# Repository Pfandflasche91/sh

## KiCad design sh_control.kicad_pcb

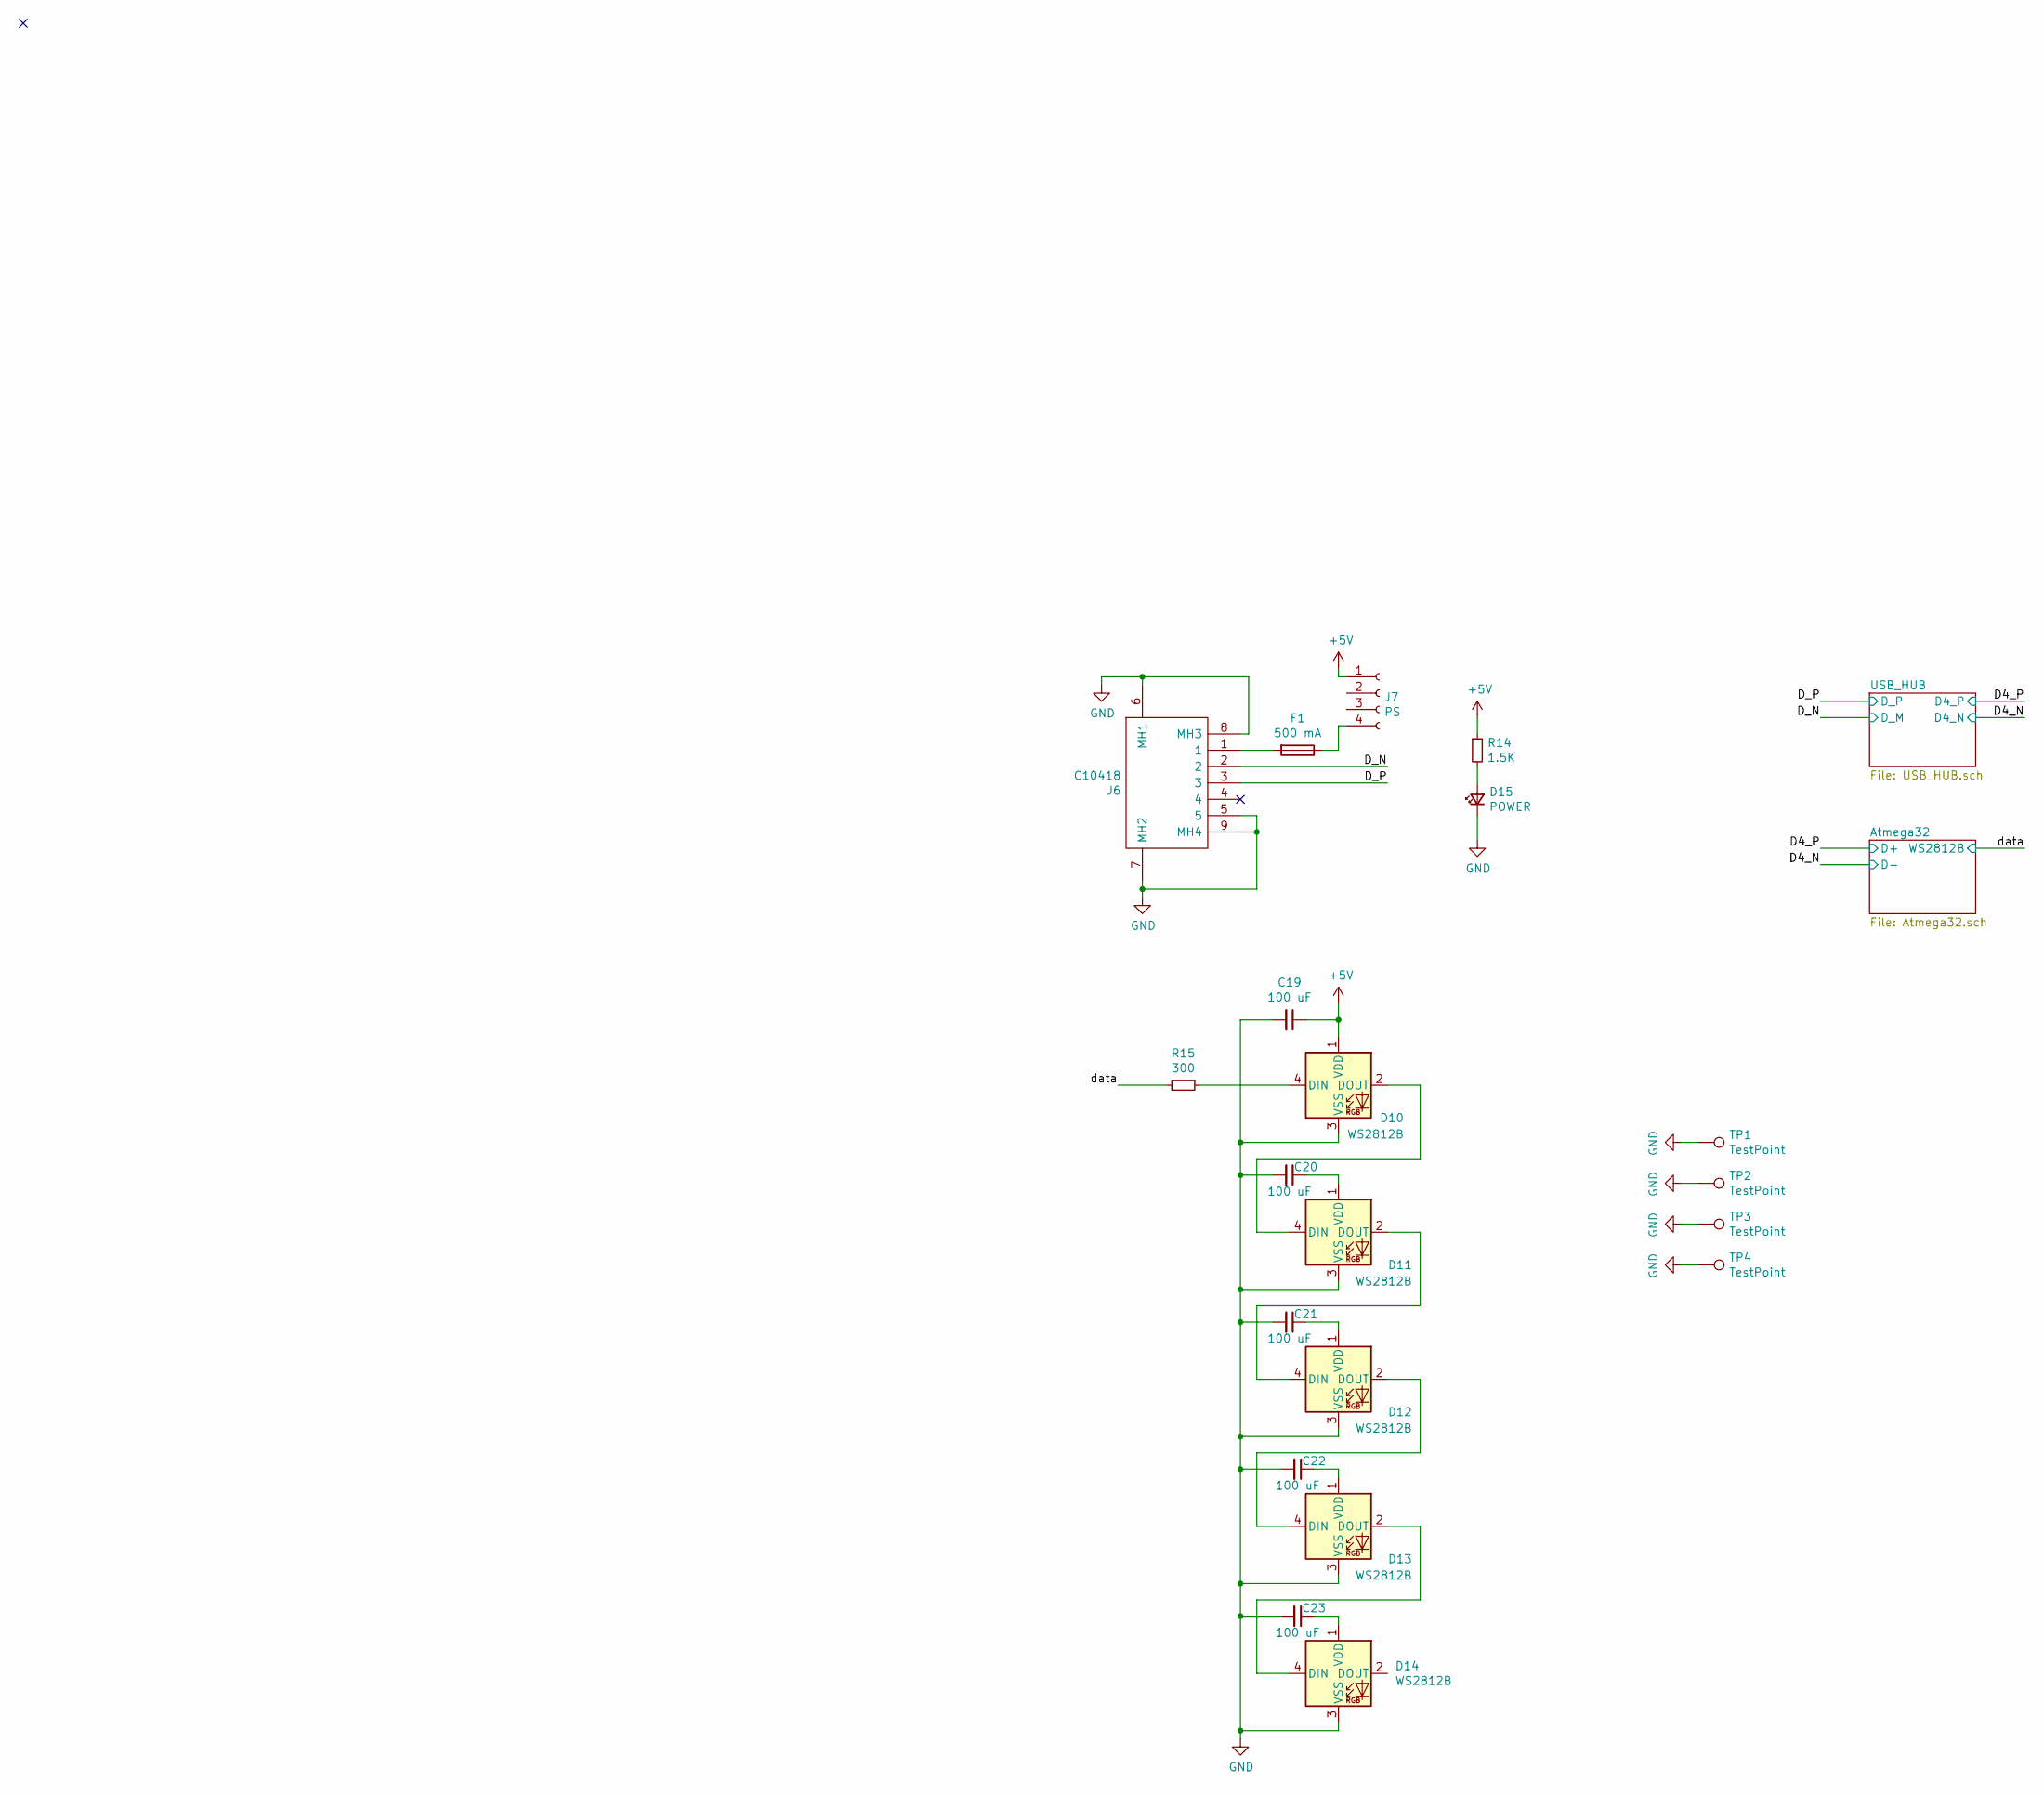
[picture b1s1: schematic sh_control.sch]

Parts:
C19, C20, C21, C22, C23: 100 uF; C_1210_3225Metric; LCSC Part # C90143
D10, D11, D12, D13, D14: WS2812B; LED_WS2812B_PLCC4_5.0x5.0mm_P3.2mm
D15: POWER; LED_0603_1608Metric; LCSC Part # C72043
F1: 500 mA; Fuse_1812_4532Metric; LCSC Part # C117855
J6: C10418; Manufacturer_Part_Number C10418; LCSC Part # C10418
J7: PS; JST_XH_S4B-XH-A-1_1x04_P2.50mm_Horizontal; LCSC Part # C163037
R14: 1.5K; R_0603_1608Metric; LCSC Part # C22843
R15: 300; R_0603_1608Metric; LCSC Part # C23138
TP1, TP2, TP3, TP4: TestPoint; MountingHole_2.2mm_M2_Pad_Via

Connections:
+5V: C19.1, D10.1 (VDD), J7.1, R14.1; also elsewhere on the board
/D_N: J6.2; also elsewhere on the board
/D_P: J6.3; also elsewhere on the board
/data: R15.2; also elsewhere on the board
GND: C19.2, C20.2, C21.2, C22.2, C23.2, D10.3 (VSS), D11.3 (VSS), D12.3 (VSS), D13.3 (VSS), D14.3 (VSS), D15.1 (K), J6.5, J6.6 (MH1), J6.7 (MH2), J6.8 (MH3), J6.9 (MH4), TP1.1, TP2.1, TP3.1, TP4.1; also elsewhere on the board
unnamed: C20.1, D11.1 (VDD)
unnamed: C21.1, D12.1 (VDD)
unnamed: C22.1, D13.1 (VDD)
unnamed: C23.1, D14.1 (VDD)
unnamed: D10.2 (DOUT), D11.4 (DIN)
unnamed: D10.4 (DIN), R15.1
unnamed: D11.2 (DOUT), D12.4 (DIN)
unnamed: D12.2 (DOUT), D13.4 (DIN)
unnamed: D13.2 (DOUT), D14.4 (DIN)
unnamed: D15.2 (A), R14.2
unnamed: F1.1, J7.4
unnamed: F1.2, J6.1

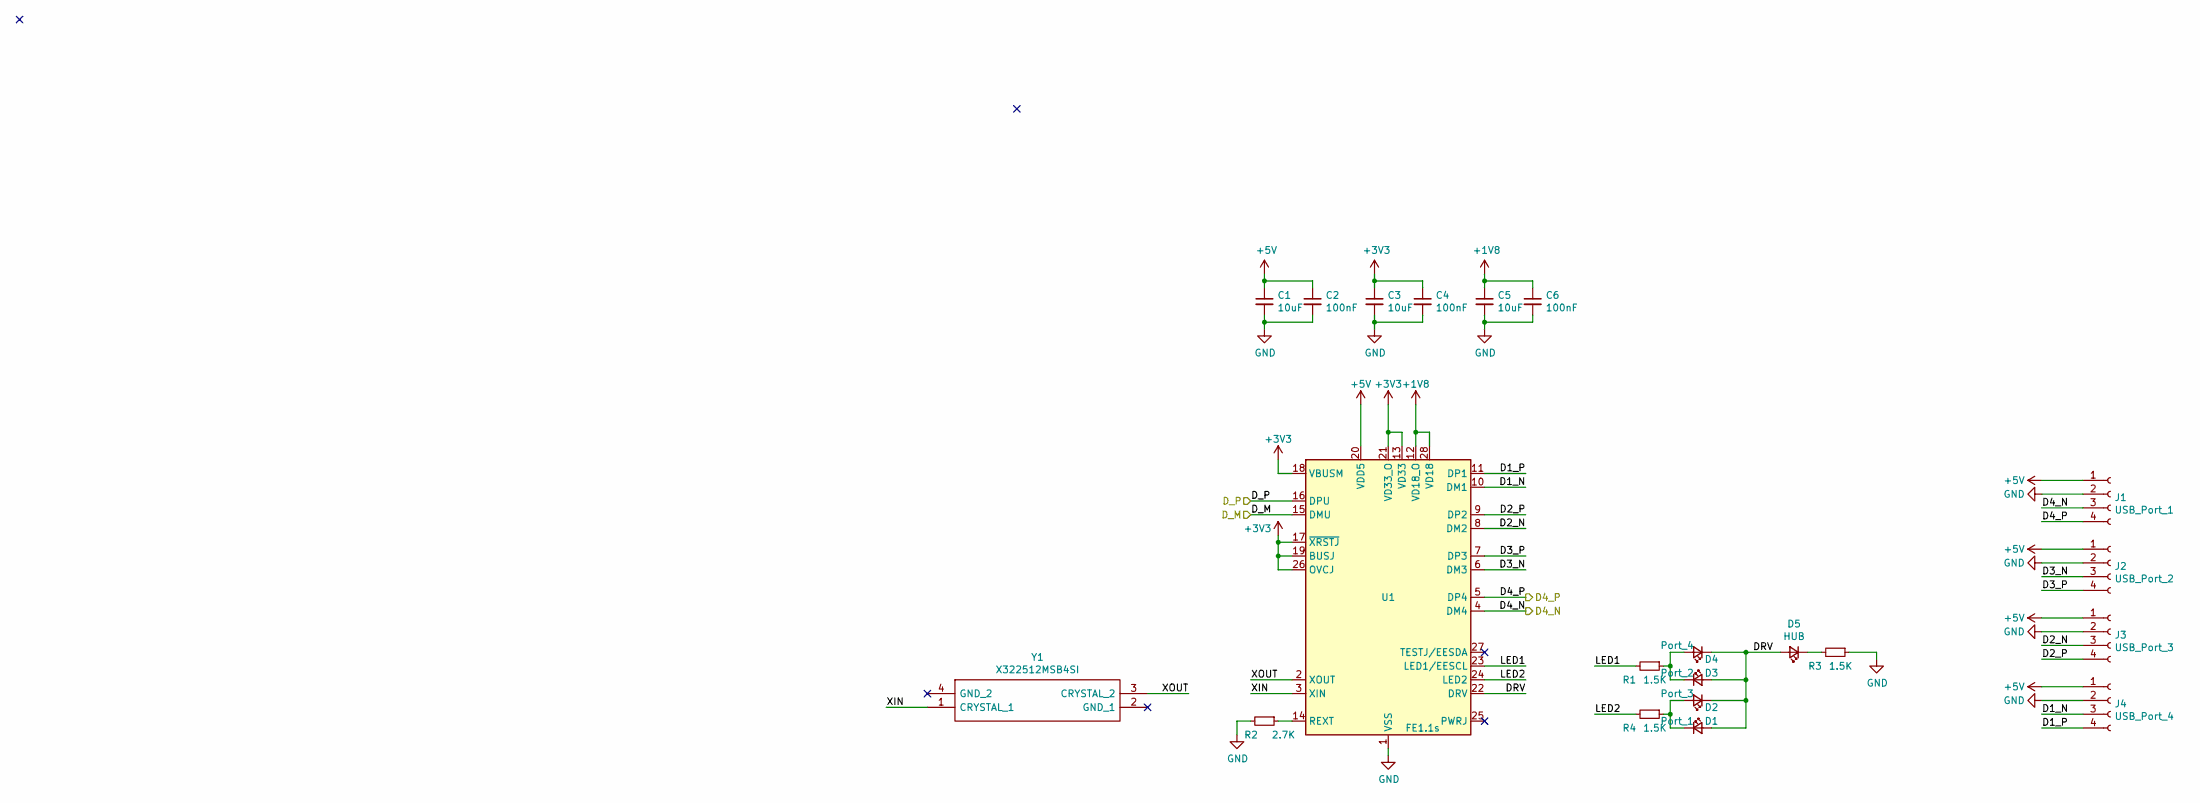
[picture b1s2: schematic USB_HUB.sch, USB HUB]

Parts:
C1, C3, C5: 10uF; C_0805_2012Metric; LCSC Part # C15850
C2, C4, C6: 100nF; C_0603_1608Metric; LCSC Part # C14663
D1: Port_1; LED_0603_1608Metric; LCSC Part # C72041
D2: Port_3; LED_0603_1608Metric; LCSC Part # C72041
D3: Port_2; LED_0603_1608Metric; LCSC Part # C72041
D4: Port_4; LED_0603_1608Metric; LCSC Part # C72041
D5: HUB; LED_0805_2012Metric_Castellated; LCSC Part # C2297
J1: USB_Port_1; JST_XH_S4B-XH-A-1_1x04_P2.50mm_Horizontal; LCSC Part # C163037
J2: USB_Port_2; JST_XH_S4B-XH-A-1_1x04_P2.50mm_Horizontal; LCSC Part # C163037
J3: USB_Port_3; JST_XH_S4B-XH-A-1_1x04_P2.50mm_Horizontal; LCSC Part # C163037
J4: USB_Port_4; JST_XH_S4B-XH-A-1_1x04_P2.50mm_Horizontal; LCSC Part # C163037
R1, R3, R4: 1.5K; R_0603_1608Metric; LCSC Part # C22843
R2: 2.7K; R_0603_1608Metric; LCSC Part # C13167
U1: FE1.1s; SSOP-28_3.9x9.9mm_P0.635mm
Y1: X322512MSB4SI; Manufacturer_Part_Number X322512MSB4SI; LCSC Part # C9002

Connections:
+1V8: C5.1, C6.1, U1.12 (VD18_O), U1.28 (VD18)
+3V3: C3.1, C4.1, U1.13 (VD33), U1.17 (~XRSTJ), U1.18 (VBUSM), U1.19 (BUSJ), U1.21 (VD33_O), U1.26 (OVCJ)
+5V: C1.1, C2.1, J1.1, J2.1, J3.1, J4.1, U1.20 (VDD5); also elsewhere on the board
/D4_N: J1.3, U1.4 (DM4); also elsewhere on the board
/D4_P: J1.4, U1.5 (DP4); also elsewhere on the board
/D_N: U1.15 (DMU); also elsewhere on the board
/D_P: U1.16 (DPU); also elsewhere on the board
/USB_HUB/D1_N: J4.3, U1.10 (DM1)
/USB_HUB/D1_P: J4.4, U1.11 (DP1)
/USB_HUB/D2_N: J3.3, U1.8 (DM2)
/USB_HUB/D2_P: J3.4, U1.9 (DP2)
/USB_HUB/D3_N: J2.3, U1.6 (DM3)
/USB_HUB/D3_P: J2.4, U1.7 (DP3)
/USB_HUB/DRV: D1.2 (A), D2.1 (K), D3.2 (A), D4.1 (K), D5.2 (A), U1.22 (DRV)
/USB_HUB/LED1: R1.2, U1.23 (LED1/EESCL)
/USB_HUB/LED2: R4.2, U1.24 (LED2)
/USB_HUB/XIN: U1.3 (XIN), Y1.1 (CRYSTAL_1)
/USB_HUB/XOUT: U1.2 (XOUT), Y1.3 (CRYSTAL_2)
GND: C1.2, C2.2, C3.2, C4.2, C5.2, C6.2, J1.2, J2.2, J3.2, J4.2, R2.2, R3.1, U1.1 (VSS); also elsewhere on the board
unnamed: D1.1 (K), D2.2 (A), R4.1
unnamed: D3.1 (K), D4.2 (A), R1.1
unnamed: D5.1 (K), R3.2
unnamed: R2.1, U1.14 (REXT)

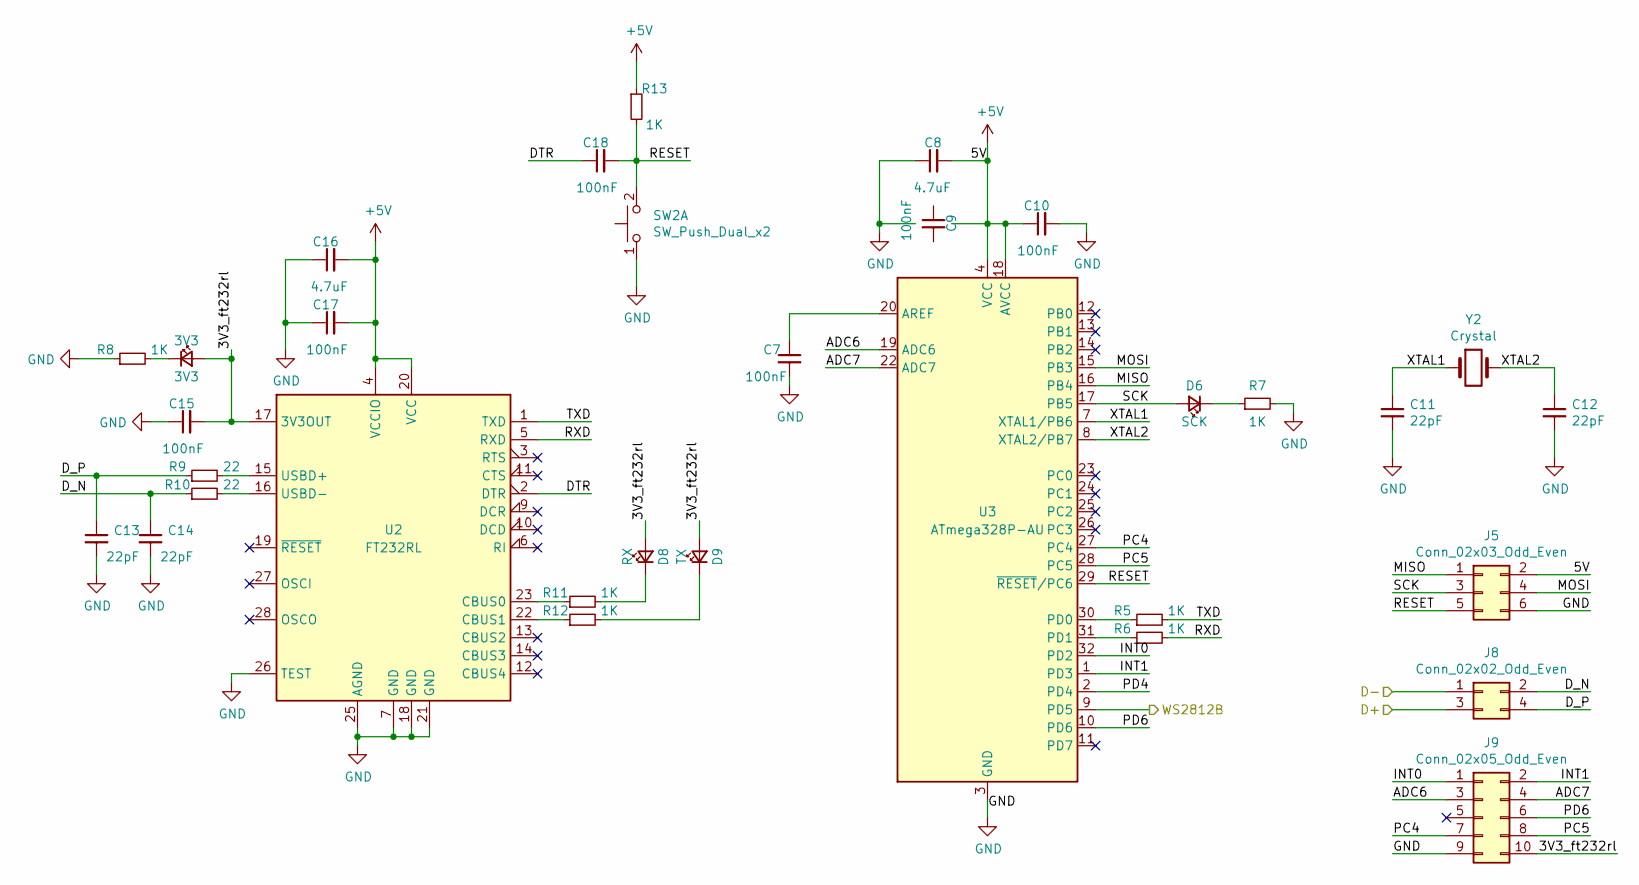
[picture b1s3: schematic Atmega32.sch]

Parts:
3V3: 3V3; LED_0603_1608Metric; LCSC Part # C72043
C7, C9, C10, C15, C17, C18: 100nF; C_0603_1608Metric; LCSC Part # C14663
C8, C16: 4.7uF; C_1206_3216Metric; LCSC Part # C29823
C11, C12, C13, C14: 22pF; C_0603_1608Metric; LCSC Part # C1603
D6: SCK; LED_0603_1608Metric; LCSC Part # C2286
D8: RX; LED_0603_1608Metric; LCSC Part # C2286
D9: TX; LED_0603_1608Metric; LCSC Part # C2286
J5: Conn_02x03_Odd_Even; PinHeader_2x03_P2.00mm_Vertical; LCSC Part # C225288
J8: Conn_02x02_Odd_Even; PinHeader_2x02_P2.00mm_Vertical; LCSC Part # C225287
J9: Conn_02x05_Odd_Even; PinHeader_2x05_P2.00mm_Vertical; LCSC Part # C225290
R5, R6, R7, R8, R11, R12, R13: 1K; R_0603_1608Metric; LCSC Part # C21190
R9, R10: 22; R_0603_1608Metric; LCSC Part # C23345
SW2: SW_Push_Dual_x2; SW_PUSH_6mm_H4.3mm
U2: FT232RL; SSOP-28_5.3x10.2mm_P0.65mm
U3: ATmega328P-AU; TQFP-32_7x7mm_P0.8mm; LCSC Part # C14877
Y2: Crystal; Crystal_SMD_HC49-SD

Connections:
+5V: C8.2, C10.1, C16.2, C17.2, J5.2, R13.1, U2.4 (VCCIO), U2.20 (VCC), U3.4 (VCC), U3.6 (VCC), U3.18 (AVCC); also elsewhere on the board
/Atmega32/3V3_ft232rl: 3V3.2 (A), C15.2, D8.2 (A), D9.2 (A), J9.10, U2.17 (3V3OUT)
/Atmega32/ADC6: J9.3, U3.19 (ADC6)
/Atmega32/ADC7: J9.4, U3.22 (ADC7)
/Atmega32/DTR: C18.1, U2.2 (DTR)
/Atmega32/D_N: C14.1, J8.2, R10.1
/Atmega32/D_P: C13.1, J8.4, R9.1
/Atmega32/INT0: J9.1, U3.32 (PD2)
/Atmega32/INT1: J9.2, U3.1 (PD3)
/Atmega32/MISO: J5.1, U3.16 (PB4)
/Atmega32/MOSI: J5.4, U3.15 (PB3)
/Atmega32/PC4: J9.7, U3.27 (PC4)
/Atmega32/PC5: J9.8, U3.28 (PC5)
/Atmega32/PD4: U3.2 (PD4)
/Atmega32/PD6: J9.6, U3.10 (PD6)
/Atmega32/RESET: C18.2, J5.5, R13.2, SW2.2 (D), U3.29 (~RESET~/PC6)
/Atmega32/RXD: R6.2, U2.5 (RXD)
/Atmega32/SCK: D6.2 (A), J5.3, U3.17 (PB5)
/Atmega32/TXD: R5.2, U2.1 (TXD)
/Atmega32/XTAL1: C11.1, U3.7 (XTAL1/PB6), Y2.1
/Atmega32/XTAL2: C12.1, U3.8 (XTAL2/PB7), Y2.2
/D4_N: J8.1; also elsewhere on the board
/D4_P: J8.3; also elsewhere on the board
/data: U3.9 (PD5); also elsewhere on the board
GND: C7.2, C8.1, C10.2, C11.2, C12.2, C13.2, C14.2, C15.1, C16.1, C17.1, J5.6, J9.9, R7.2, R8.1, SW2.1 (C), U2.7 (GND), U2.18 (GND), U2.21 (GND), U2.25 (AGND), U2.26 (TEST), U3.3 (GND), U3.5 (GND), U3.21 (GND); also elsewhere on the board
unnamed: 3V3.1 (K), R8.2
unnamed: C7.1, U3.20 (AREF)
unnamed: D6.1 (K), R7.1
unnamed: D8.1 (K), R11.2
unnamed: D9.1 (K), R12.2
unnamed: R5.1, U3.30 (PD0)
unnamed: R6.1, U3.31 (PD1)
unnamed: R9.2, U2.15 (USBD+)
unnamed: R10.2, U2.16 (USBD-)
unnamed: R11.1, U2.23 (CBUS0)
unnamed: R12.1, U2.22 (CBUS1)

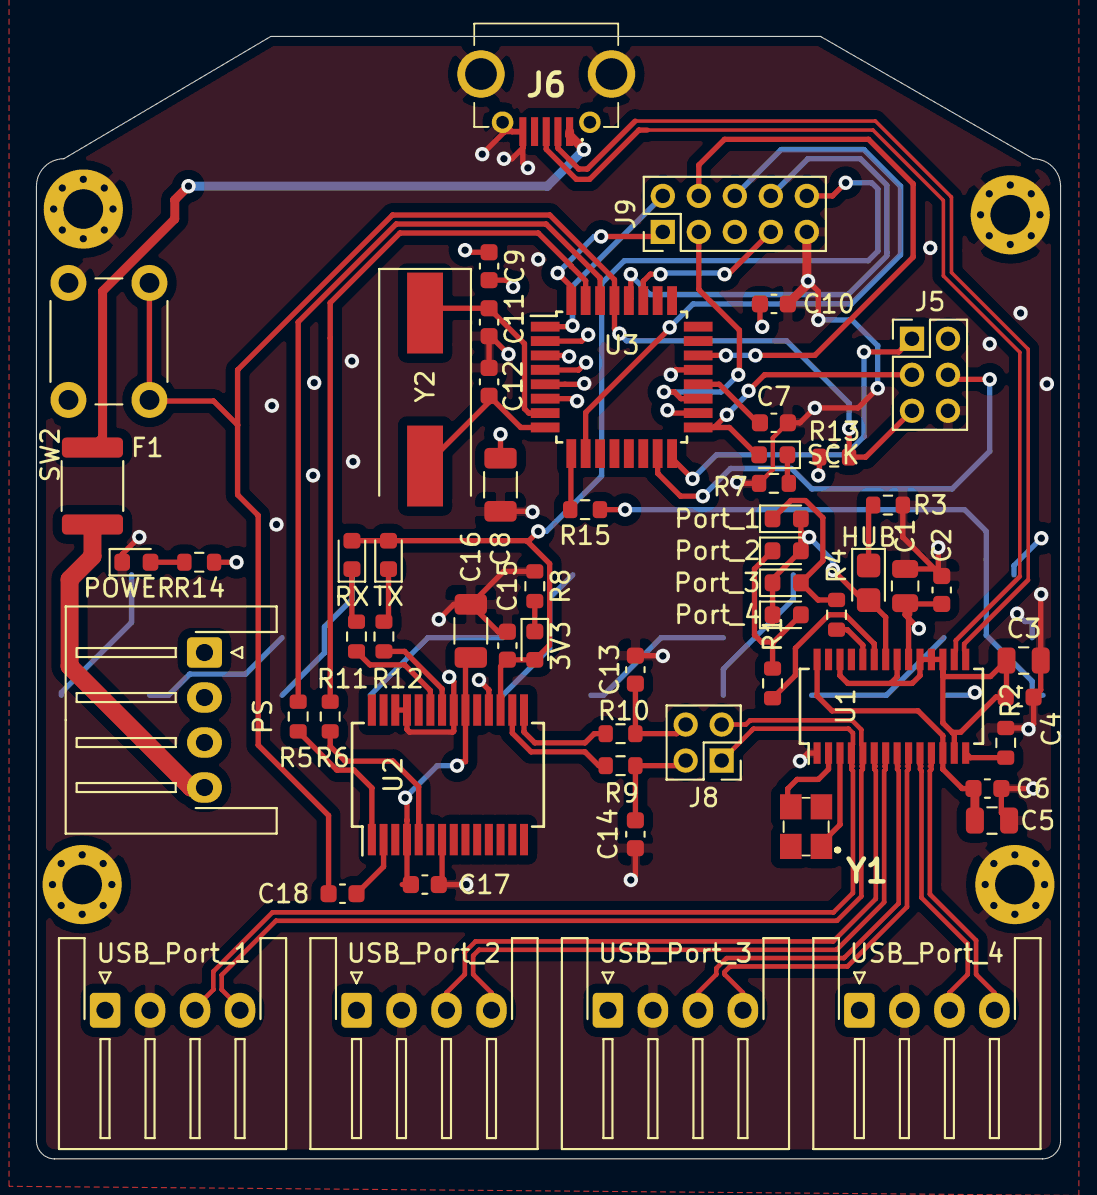
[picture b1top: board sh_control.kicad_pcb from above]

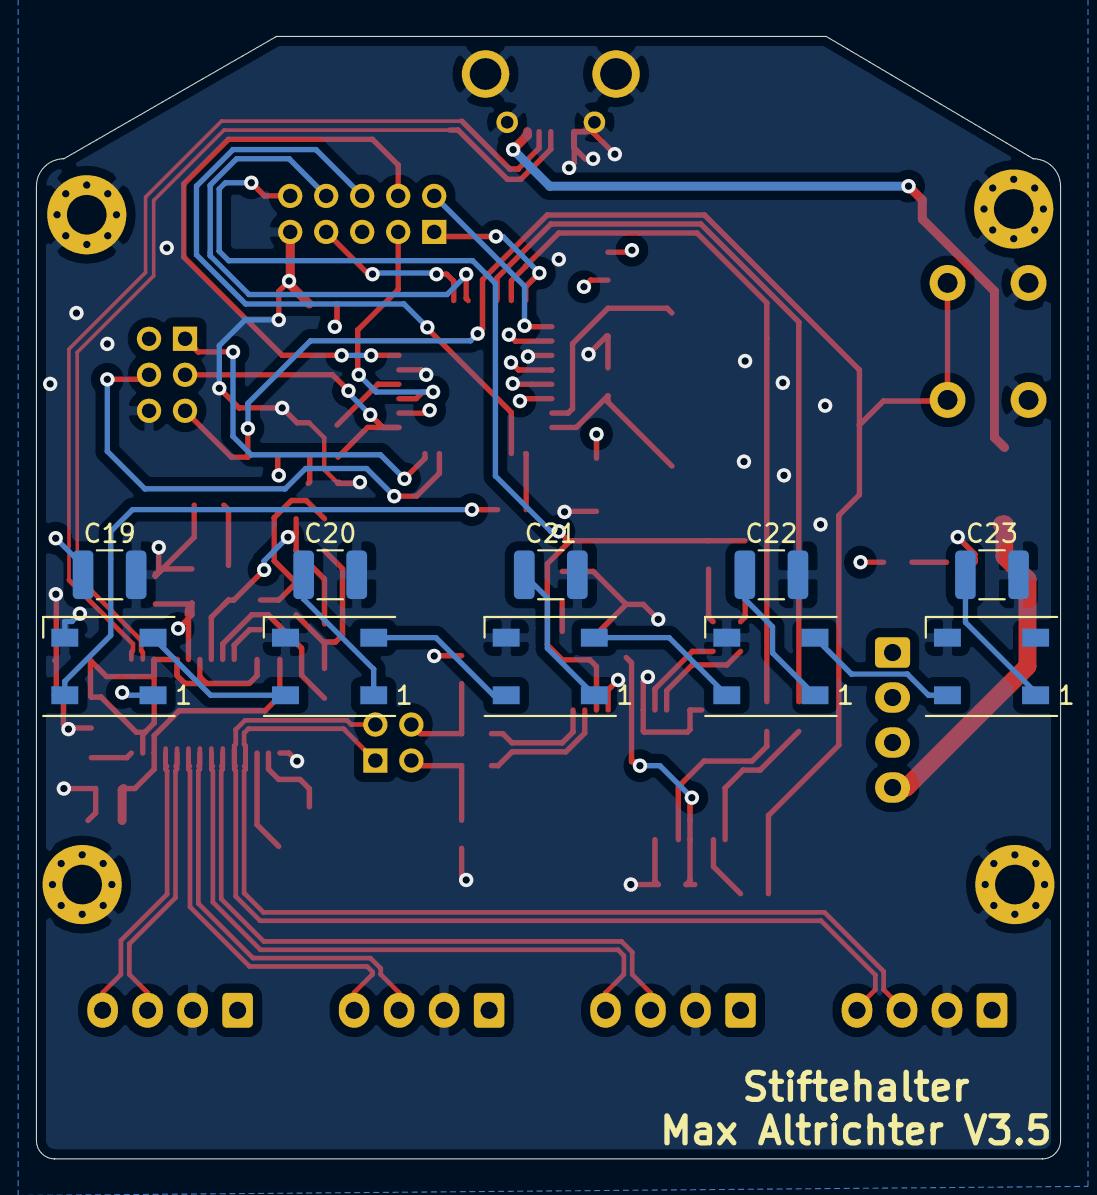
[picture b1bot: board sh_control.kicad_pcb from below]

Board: 4 copper layers, 56.9 x 62.4 mm, 73 parts (10 on the bottom side), 66 nets.

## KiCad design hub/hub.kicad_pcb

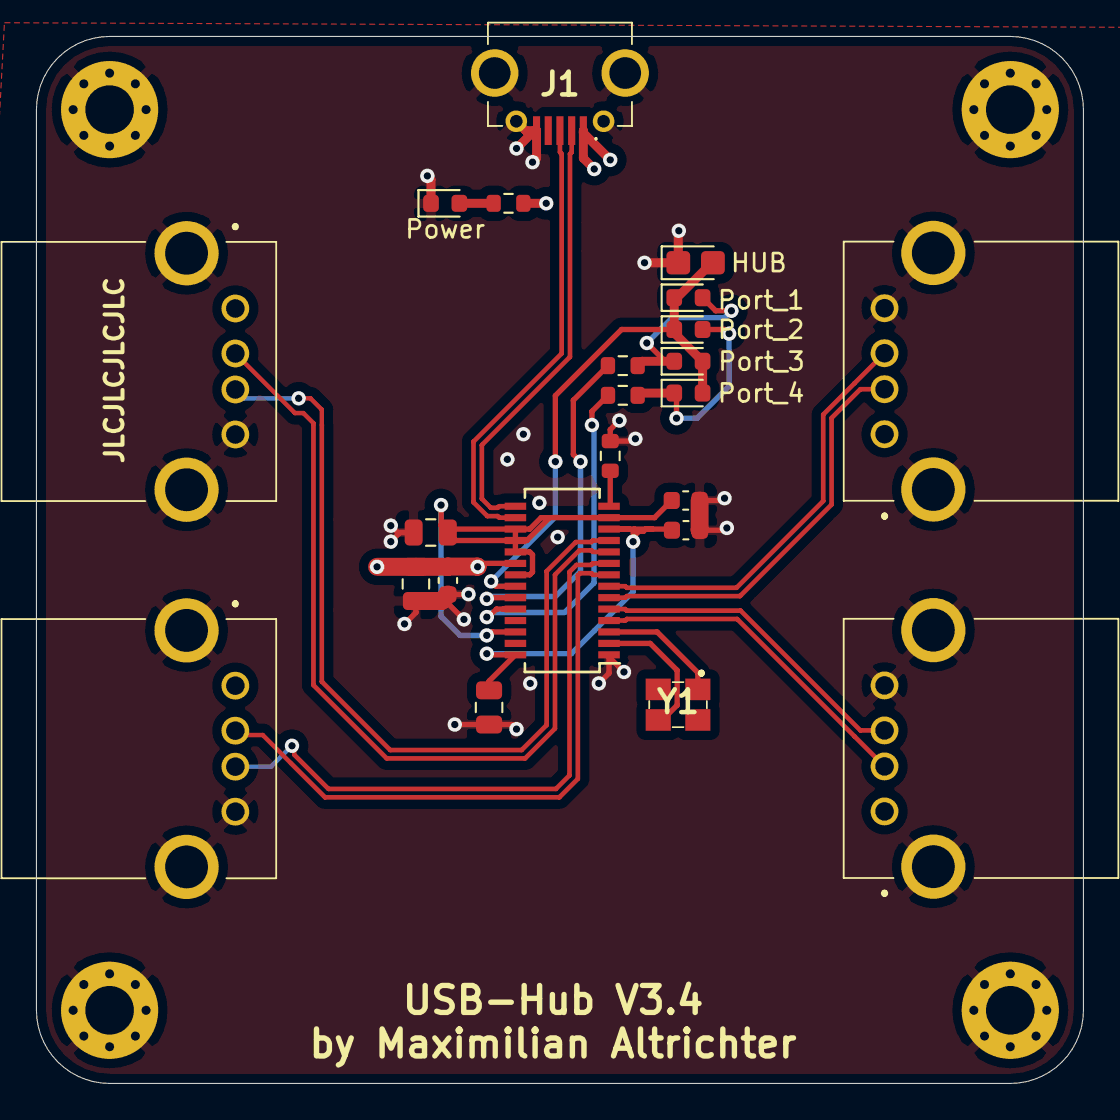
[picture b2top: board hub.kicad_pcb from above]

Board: 4 copper layers, 58.2 x 58.2 mm, 27 parts (0 on the bottom side), 23 nets.

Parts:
C1, C3, C5: 100nF; C_0603_1608Metric
C2, C4, C6: 10uF; C_0805_2012Metric
D1: Power; LED_0603_1608Metric
D2: Port_1; LED_0603_1608Metric
D3: Port_3; LED_0603_1608Metric
D4: Port_2; LED_0603_1608Metric
D5: Port_4; LED_0603_1608Metric
D6: HUB; LED_0805_2012Metric_Castellated
H1, H2, H3, H4: MountingHole_Pad; MountingHole_2.7mm_M2.5_Pad_Via
J1: C10418
J2, J3, J4, J5: USB_A; 676430910
R1, R3, R4: 1.5K; R_0603_1608Metric
R2: 2.7K; R_0603_1608Metric
U1: FE1.1s; SSOP-28_3.9x9.9mm_P0.635mm
Y1: 12 MHZ; X322512MSB4SI

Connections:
+1V8: C5.1, C6.1, U1.12, U1.28
+3V3: C3.1, C4.1, U1.13, U1.17, U1.18, U1.19, U1.21, U1.26
+5V: C1.1, C2.1, J1.1, J2.1, J3.1, J4.1, J5.1, R1.1, U1.20
/D1_N: J2.2, U1.10
/D1_P: J2.3, U1.11
/D2_N: J3.2, U1.8
/D2_P: J3.3, U1.9
/D3_N: J5.2, U1.6
/D3_P: J5.3, U1.7
/D4_N: J4.2, U1.4
/D4_P: J4.3, U1.5
/DRV: D2.1, D3.2, D4.1, D5.2, D6.2, U1.22
/D_N: J1.2, U1.15
/D_P: J1.3, U1.16
/LED_1: R3.1, U1.23
/LED_2: R4.1, U1.24
/XIN: U1.3, Y1.1
/XOUT: U1.2, Y1.3
GND: C1.2, C2.2, C3.2, C4.2, C5.2, C6.2, D1.1, D6.1, H1.1, H2.1, H3.1, H4.1, J1.5, J1.6, J1.7, J1.8, J1.9, J2.4, J2.5, J3.4, J3.5, J4.4, J4.5, J5.4, J5.5, R2.1, U1.1
unnamed: D1.2, R1.2
unnamed: D2.2, D3.1, R3.2
unnamed: D4.2, D5.1, R4.2
unnamed: R2.2, U1.14

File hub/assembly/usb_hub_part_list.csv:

Comment,Designator,Footprint,LCSC
"100nF","C1,C3,C5","Capacitor_SMD:C_0603_1608Metric","C14663"
"10uF","C2,C4,C6","Capacitor_SMD:C_0805_2012Metric","C15850"
"Power","D1","LED_SMD:LED_0603_1608Metric","C72043"
"Port_1","D2","LED_SMD:LED_0603_1608Metric","C72041"
"Port_3","D3","LED_SMD:LED_0603_1608Metric","C72041"
"Port_2","D4","LED_SMD:LED_0603_1608Metric","C72041"
"Port_4","D5","LED_SMD:LED_0603_1608Metric","C72041"
"HUB","D6","LED_SMD:LED_0805_2012Metric_Castellated","C84256"
"1.5K","R1,R3,R4","Resistor_SMD:R_0603_1608Metric","C22843"
"2.7K","R2","Resistor_SMD:R_0603_1608Metric","C13167"
"12 MHZ","Y1","crystal_12MHz:X322512MSB4SI","C9002"
"C10418","J1","usb_b_micro:C10418","C10418"
"USB_A","J2","SamacSys_Parts:676430910","C42664"
"USB_A","J3","SamacSys_Parts:676430910","C42664"
"USB_A","J4","SamacSys_Parts:676430910","C42664"
"USB_A","J5","SamacSys_Parts:676430910","C42664"

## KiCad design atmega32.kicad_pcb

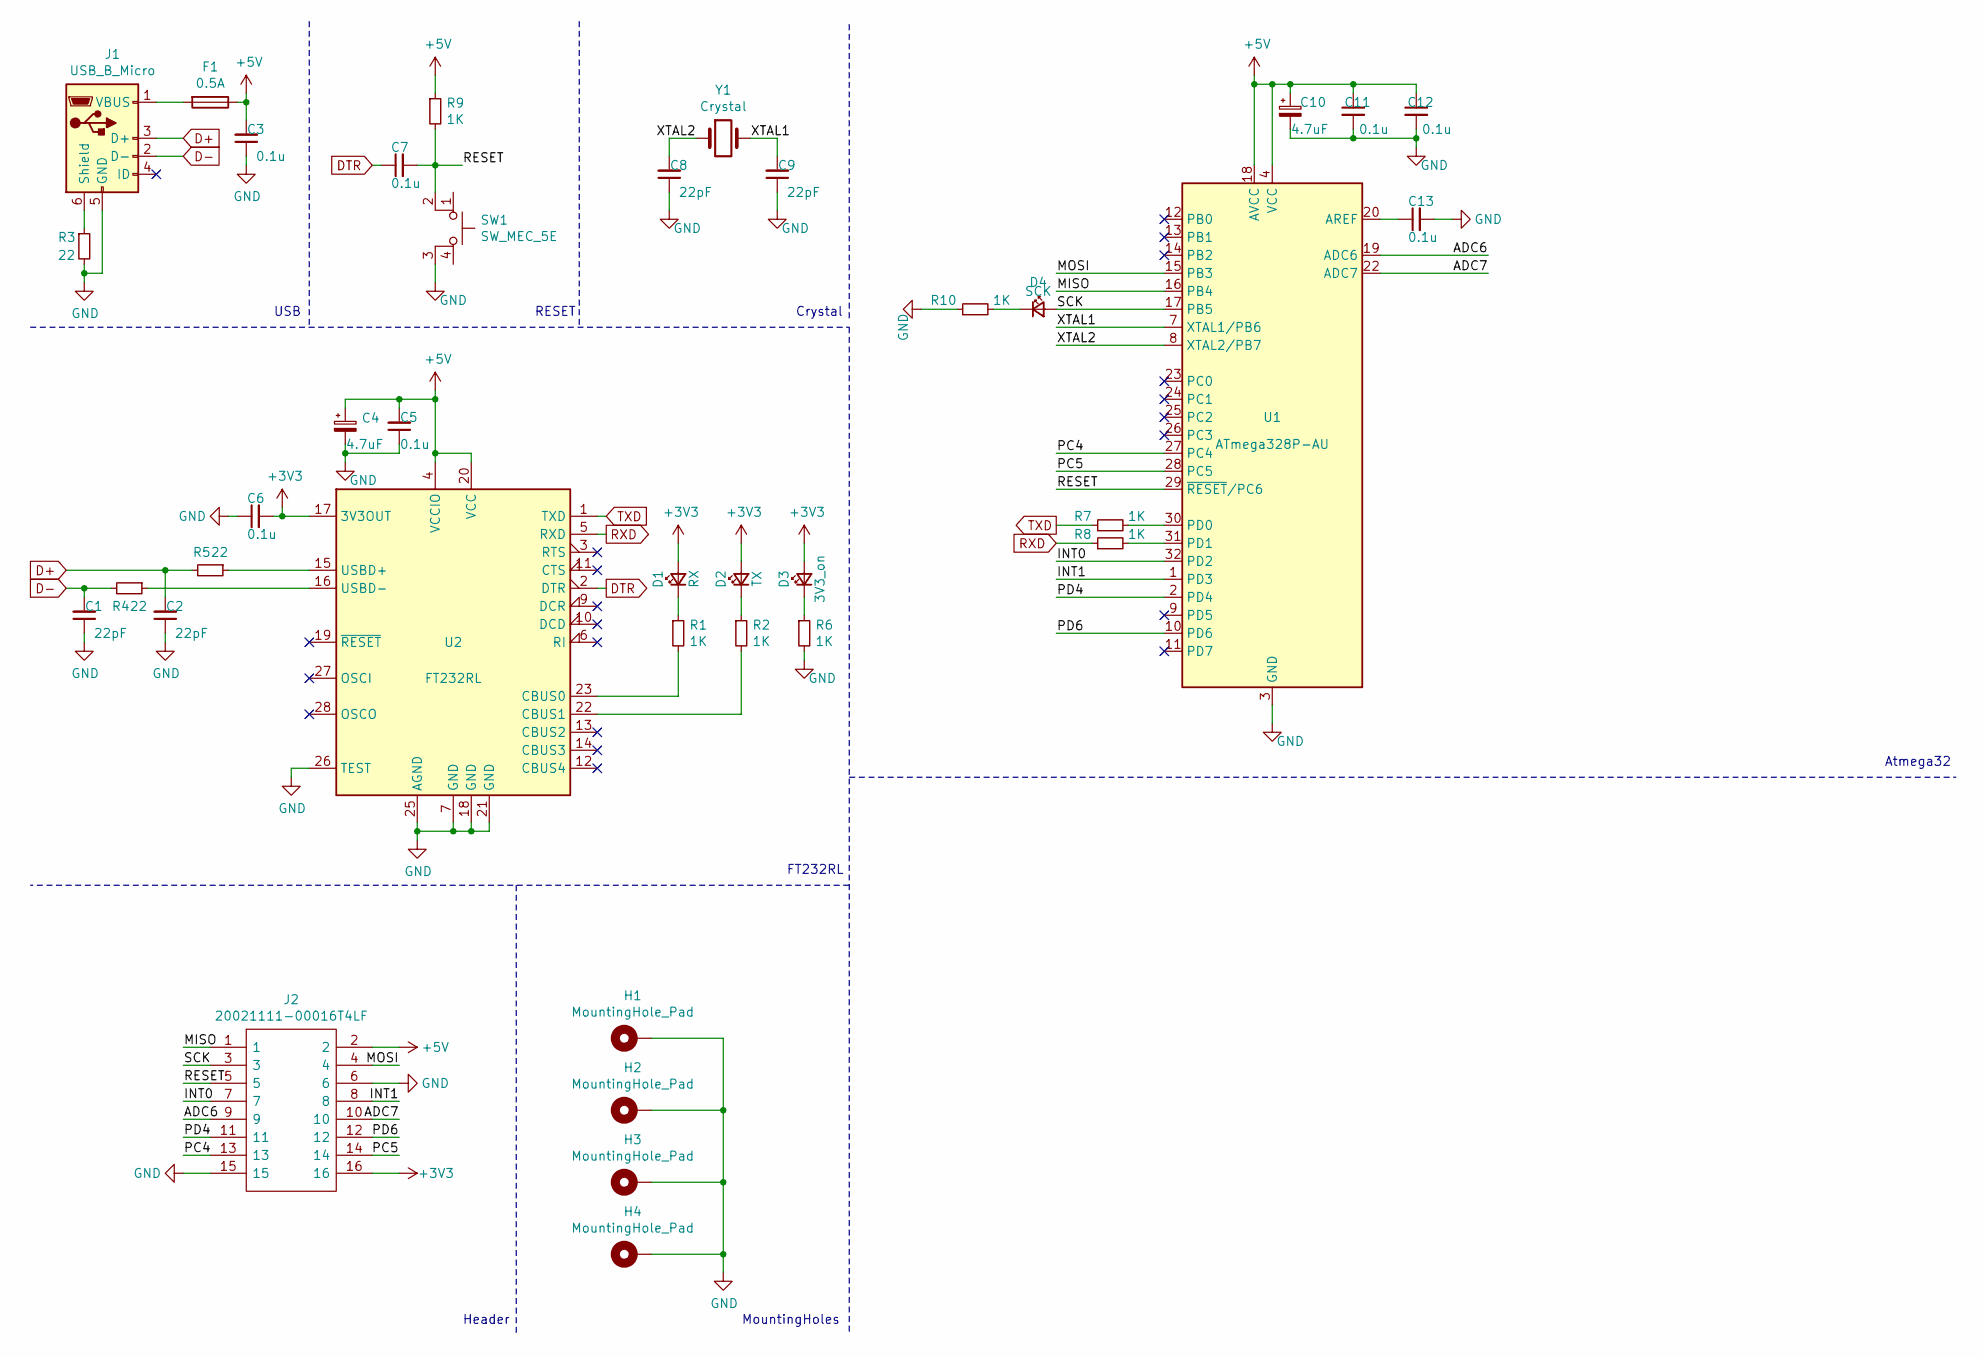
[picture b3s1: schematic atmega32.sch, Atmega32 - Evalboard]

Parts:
C1, C2: 22pF; C_22pF
C3, C5, C6, C7, C11, C12, C13: 0.1u; C_0.1uF
C4, C10: 4.7uF; C_4.7uF
C8, C9: 22pF; C_0.1uF
D1: RX; LED_WL-SMCW
D2: TX; LED_WL-SMCW
D3: 3V3_on; LED_WL-SMCW
D4: SCK; LED_WL-SMCW
F1: 0.5A; F_0.5A
H1, H2, H3, H4: MountingHole_Pad; MountingHole_3.2mm_M3_Pad_Via
J1: USB_B_Micro; USB_Micro-B_Molex-105017-0001
J2: 20021111-00016T4LF; 2002111100016T4LF; Mouser Part Number 649-221111-00016T4LF
R1, R2, R6, R7, R8, R9, R10: 1K; R_1K
R3, R4, R5: 22; R_22
SW1: SW_MEC_5E; Button
U1: ATmega328P-AU; TQFP-32_7x7mm_P0.8mm
U2: FT232RL; SSOP-28_5.3x10.2mm_P0.65mm
Y1: Crystal; ECS49205PXTR

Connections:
+3V3: C6.2, D1.2 (A), D2.2 (A), D3.2 (A), J2.16, U2.17 (3V3OUT)
+5V: C3.2, C4.1, C5.2, C10.1, C11.1, C12.1, F1.1, J2.2, R9.1, U1.4 (VCC), U1.6 (VCC), U1.18 (AVCC), U2.4 (VCCIO), U2.20 (VCC)
/ADC6: J2.9, U1.19 (ADC6)
/ADC7: J2.10, U1.22 (ADC7)
/INT0: J2.7, U1.32 (PD2)
/INT1: J2.8, U1.1 (PD3)
/MISO: J2.1, U1.16 (PB4)
/MOSI: J2.4, U1.15 (PB3)
/PC4: J2.13, U1.27 (PC4)
/PC5: J2.14, U1.28 (PC5)
/PD4: J2.11, U1.2 (PD4)
/PD6: J2.12, U1.10 (PD6)
/RESET: C7.2, J2.5, R9.2, SW1.2, U1.29 (~RESET~/PC6)
/SCK: D4.2 (A), J2.3, U1.17 (PB5)
/XTAL1: C9.2, U1.7 (XTAL1/PB6), Y1.2
/XTAL2: C8.2, U1.8 (XTAL2/PB7), Y1.1
D+: C2.2, J1.3 (D+), R5.2
D-: C1.2, J1.2 (D-), R4.2
DTR: C7.1, U2.2 (DTR)
GND: C1.1, C2.1, C3.1, C4.2, C5.1, C6.1, C8.1, C9.1, C10.2, C11.2, C12.2, C13.2, H1.1, H2.1, H3.1, H4.1, J1.5 (GND), J2.6, J2.15, R3.2, R6.2, R10.1, SW1.3 (K), U1.3 (GND), U1.5 (GND), U1.21 (GND), U2.7 (GND), U2.18 (GND), U2.21 (GND), U2.25 (AGND), U2.26 (TEST)
unnamed: C13.1, U1.20 (AREF)
unnamed: D1.1 (K), R1.1
unnamed: D2.1 (K), R2.1
unnamed: D3.1 (K), R6.1
unnamed: D4.1 (K), R10.2
unnamed: F1.2, J1.1 (VBUS)
unnamed: J1.6 (Shield), R3.1
unnamed: R1.2, U2.23 (CBUS0)
unnamed: R2.2, U2.22 (CBUS1)
unnamed: R4.1, U2.16 (USBD-)
unnamed: R5.1, U2.15 (USBD+)
unnamed: R7.2, U1.30 (PD0)
unnamed: R8.2, U1.31 (PD1)
RXD: R8.1, U2.5 (RXD)
TXD: R7.1, U2.1 (TXD)

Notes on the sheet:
USB
FT232RL
Header
MountingHoles
RESET
Crystal
Atmega32

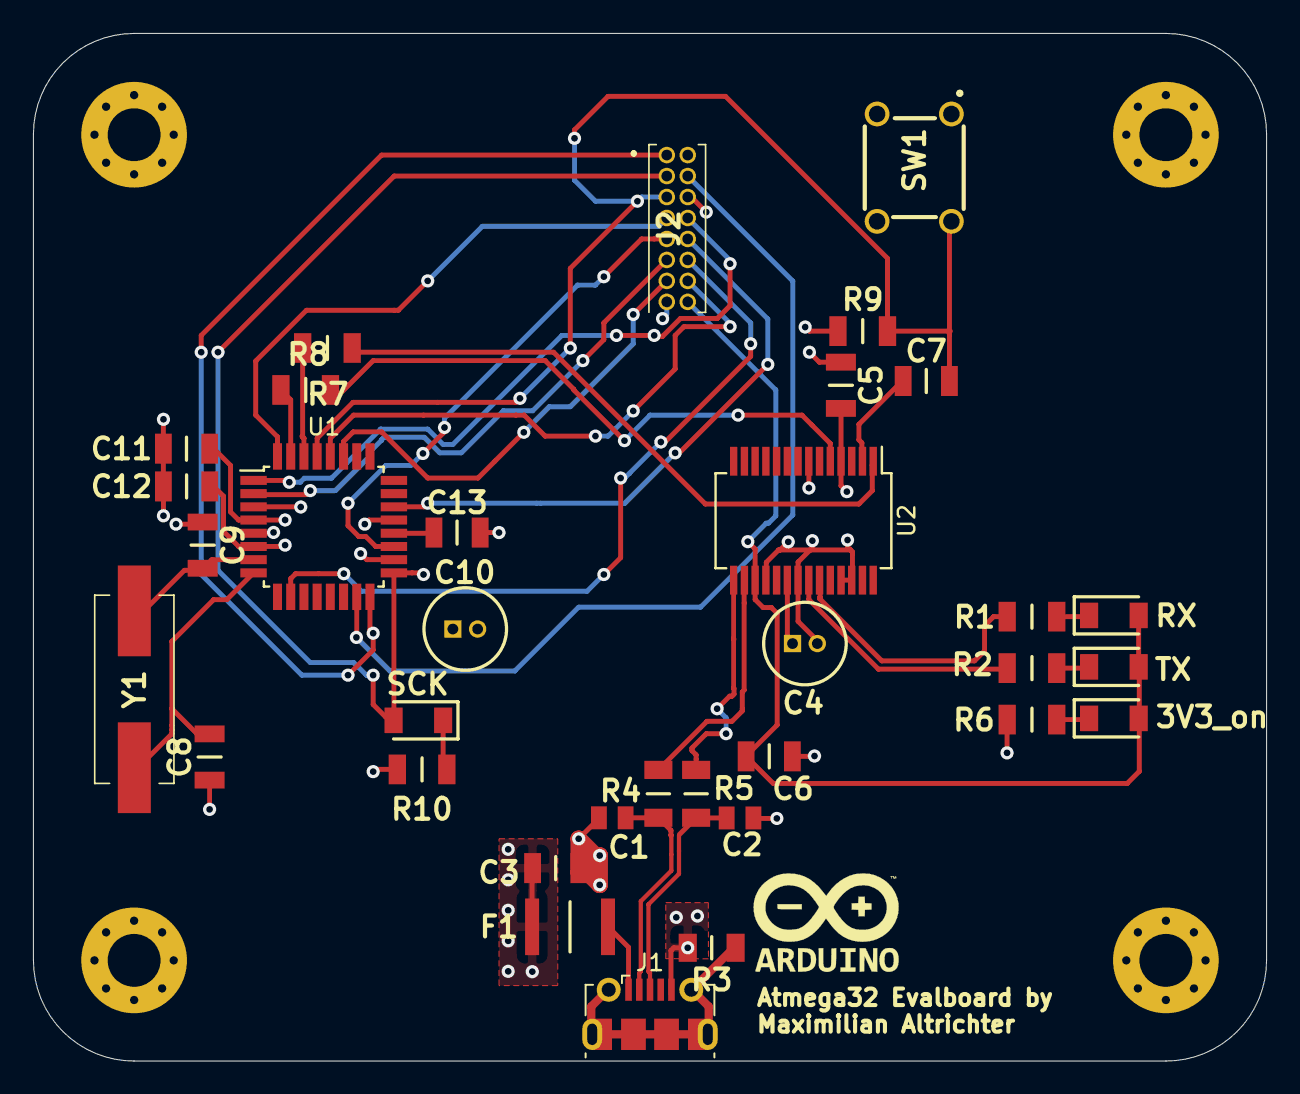
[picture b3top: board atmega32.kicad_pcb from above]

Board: 4 copper layers, 74.7 x 62.2 mm, 38 parts (0 on the bottom side), 35 nets.

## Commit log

2021-04-16 Added KiCAD files
2021-04-28 first assembly, didnt work so well
2021-04-28 deleted all, beginning of eval board
2021-04-28 hub schematic finished
2021-04-29 split in two boards from now on
2021-04-29 new branch, only for usb hub
2021-04-29 finished schematic, placing parts and so on
2021-04-30 finished hub, added reste button
2021-05-01 review passed, bom created
2021-05-01 evalboard for atmeag32
2021-05-01 gerber created -> Finished!!
2021-05-01 new project for atmgea evalboard
2021-05-01 finished eval board
2021-05-02 orderd
2021-05-13 added BOM
2021-05-13 final assembly, WORKING!!!!
2021-05-13 added stepfile
2021-05-24 start V3.3
2021-06-24 changed
2021-08-08 V3.4
2021-08-09 got all parts except usb a
2021-08-09 V3.4 finished and ordered
2021-08-09 V3.4 edit
2021-08-26 sh_control 2.0
    deleted old files and created new project
2021-08-26 USB HUB schematic ready
    added the schematic of the USB HUB in a seperate schematic file. All footprints are insertet and ready to layout
2021-08-31 added submodule: kicad_lib
2021-09-01 added atmega32 schematic
2021-09-07 file: finished schematic
2021-09-07 small changes to schematic
2021-09-16 pcb schematic and layout edit i.e. finished -> orderd pcb jlcpcb
2022-06-20 added arduino code and fusion 360 project
